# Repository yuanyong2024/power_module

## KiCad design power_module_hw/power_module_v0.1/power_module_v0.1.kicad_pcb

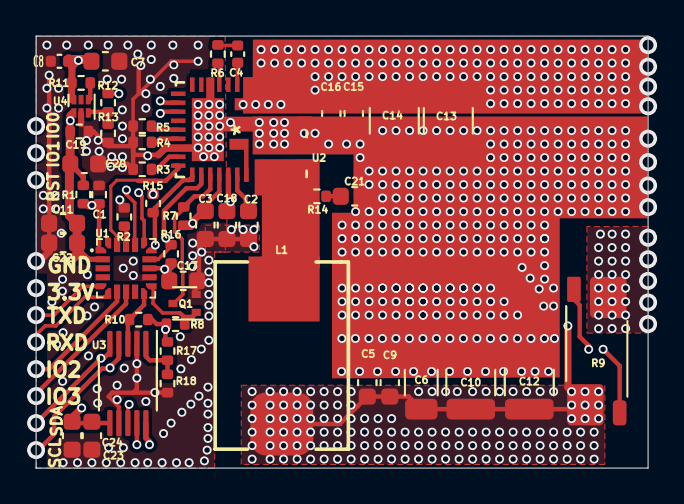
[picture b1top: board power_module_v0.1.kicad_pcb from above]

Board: 4 copper layers, 34.0 x 24.0 mm, 48 parts (0 on the bottom side), 27 nets.

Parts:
C1, C19: 0.1uF; R_0402_1005Metric
C2, C3: 1uF; C_0603_1608Metric
C4, C8: 0.1uF; C_0402_1005Metric
C5, C16, C17, C18, C21, C22, C23, C24: 0.1uF; C_0603_1608Metric
C6: 100pF; C_1206_3216Metric
C7, C11, C20: 22uF; C_0603_1608Metric
C9: 47uF; C_0603_1608Metric
C10, C12, C13, C14: 47uF; C_1210_3225Metric
C15: 10pF; C_0603_1608Metric
L1: 0.22uH; SLA100709SR22LTT
Q1: BSS138; SOT-523
R1, R5, R7, R8, R10, R11: 10K; R_0402_1005Metric
R2, R6, R18: 0R; R_0402_1005Metric
R3: 2.87K; R_0402_1005Metric
R4: 2.32K; R_0402_1005Metric
R9: 20mR; R_Shunt_Vishay_WSK2512_6332Metric_T1.19mm
R12: 31.2K 1%; R_0402_1005Metric
R13: 10K 1%; R_0402_1005Metric
R14: 1K; R_0402_1005Metric
R15, R16: 4.7K; R_0402_1005Metric
R17: NC; R_0402_1005Metric
U1: GD32E230F4V6TR; LGA20_3X3mm
U2: SiC45X; SICI450
U3: INA226; VSSOP-10_3x3mm_P0.5mm
U4: LDK130-ADJ_DFN6; DFN-6_1.3x1.2mm_P0.4mm

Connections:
+3.3V: C11.1, C17.1, C19.1, C20.1, C22.1, C23.1, C24.1, R1.2, R8.1, R10.2, R12.1, R15.2, R16.2, R17.2, U1.2 (VDDA), U1.13 (VDD), U3.6 (VS), U4.1 (OUT)
+5VA: C3.2, C7.1, C8.1, R7.1, R11.2, U2.22 (VDD), U4.6 (IN)
GNDA: C1.1, C2.1, C3.1, C5.2, C6.2, C7.2, C8.2, C9.2, C10.2, C11.2, C12.2, C13.2, C14.2, C15.2, C16.2, C17.2, C18.2, C19.2, C20.2, C21.2, C22.2, C23.2, C24.2, Q1.2 (S), R2.1, R3.1, R4.1, R5.1, R13.1, R18.1, U1.12 (VSS), U2.7 (AGND), U2.11 (VSEN-), U2.16 (AGND), U2.32 (PGND), U2.33 (PGND), U3.2 (A0), U3.7 (GND), U4.2 (GND)
I2C0_SCL: R16.1, U1.14 (PA9), U2.20 (SCL), U3.5 (SCL)
I2C0_SDA: R15.1, U1.15 (PA10), U2.19 (SDA), U3.4 (SDA)
unnamed: C4.1, R6.1
unnamed: C21.1, R14.2
unnamed: L1.1, R14.1, U2.26 (SW), U2.27 (SW), U2.28 (SW), U2.29 (SW), U2.30 (SW), U2.31 (SW)
unnamed: Q1.3 (D), R7.2, U2.21 (EN)
unnamed: R2.2, U1.18 (BOOT0)
unnamed: C1.2, R1.1, U1.1 (NRST)
unnamed: R5.2, U2.14 (ADDR)
unnamed: R6.2, U2.6 (BOOT)
unnamed: C4.2, U2.4 (PH)
unnamed: C2.2, U2.24 (PVCC)
unnamed: R3.2, U2.17 (RT/SYNC)
unnamed: C5.1, C6.1, C9.1, C10.1, C12.1, L1.2, R9.4, U2.12 (VSEN+), U3.8 (Vbus)
unnamed: R4.2, U2.15 (VSET)
unnamed: R17.1, R18.2, U3.1 (A1)
unnamed: R9.3, U3.10 (Vin+)
unnamed: R9.2, U3.9 (Vin-)
unnamed: R12.2, R13.2, U4.3 (ADJ)
unnamed: R11.1, U4.4 (EN)
PWR_ALERT: U1.19 (OSCIN), U2.18 (SALRT)
VCC: C13.1, C14.1, C15.1, C16.1, C18.1, U2.1 (PVIN), U2.2 (PVIN), U2.3 (PVIN), U2.23 (VIN), U2.34 (PVIN)
~PWR_EN: Q1.1 (G), R8.2, U1.11 (PB1)
~SENSOR_ALERT: R10.1, U1.10 (PA7), U3.3 (~Alert)

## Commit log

2024-03-31 basic placement finished for the power module
2024-04-04 update the design
2024-04-05 update the design and ship out for mfg
2024-04-05 update the bom
2025-05-04 update the design file
